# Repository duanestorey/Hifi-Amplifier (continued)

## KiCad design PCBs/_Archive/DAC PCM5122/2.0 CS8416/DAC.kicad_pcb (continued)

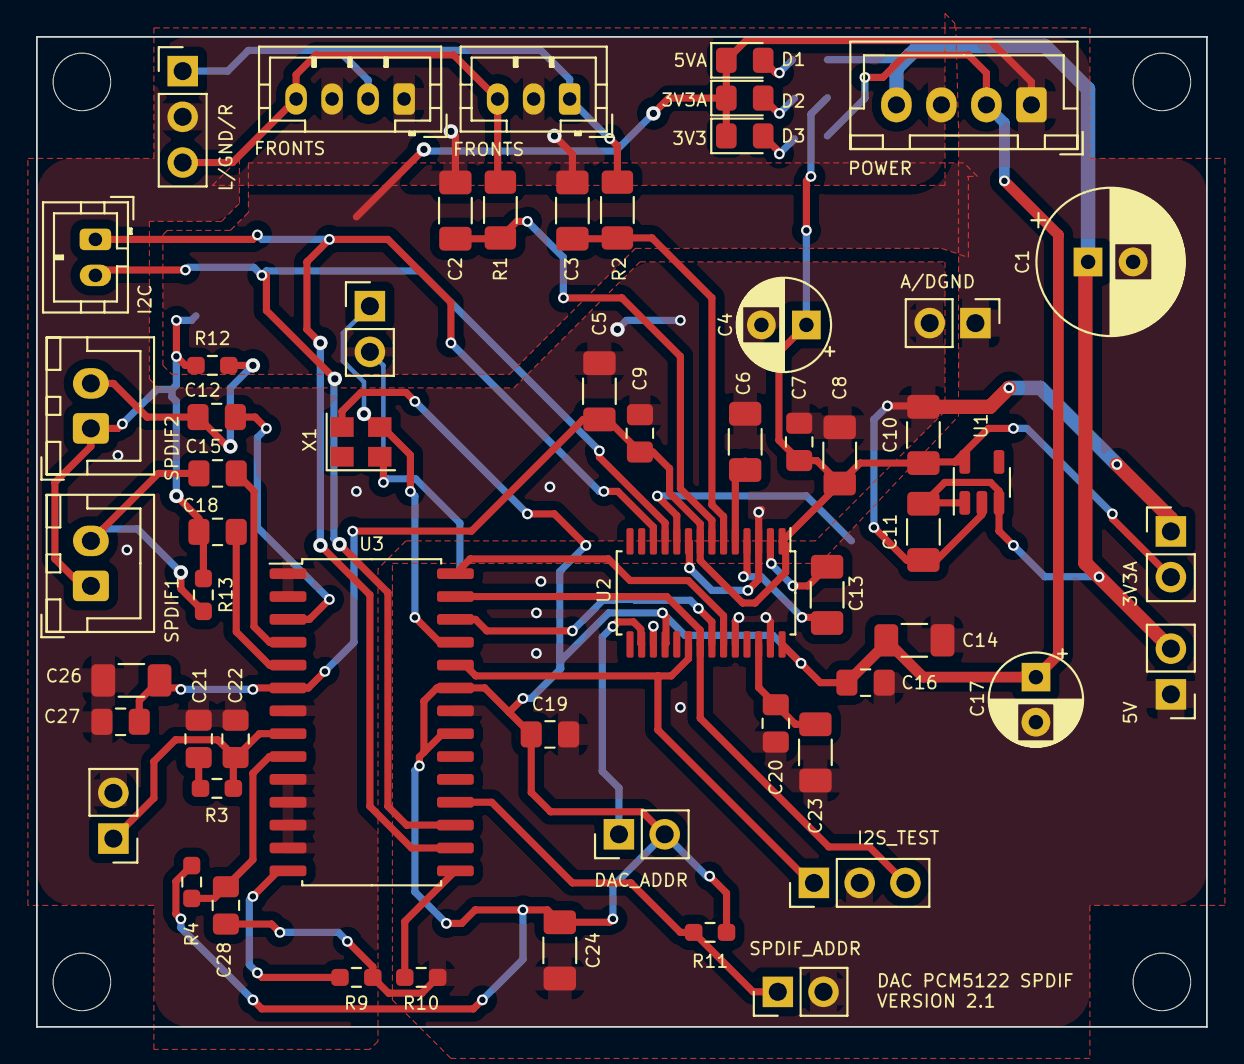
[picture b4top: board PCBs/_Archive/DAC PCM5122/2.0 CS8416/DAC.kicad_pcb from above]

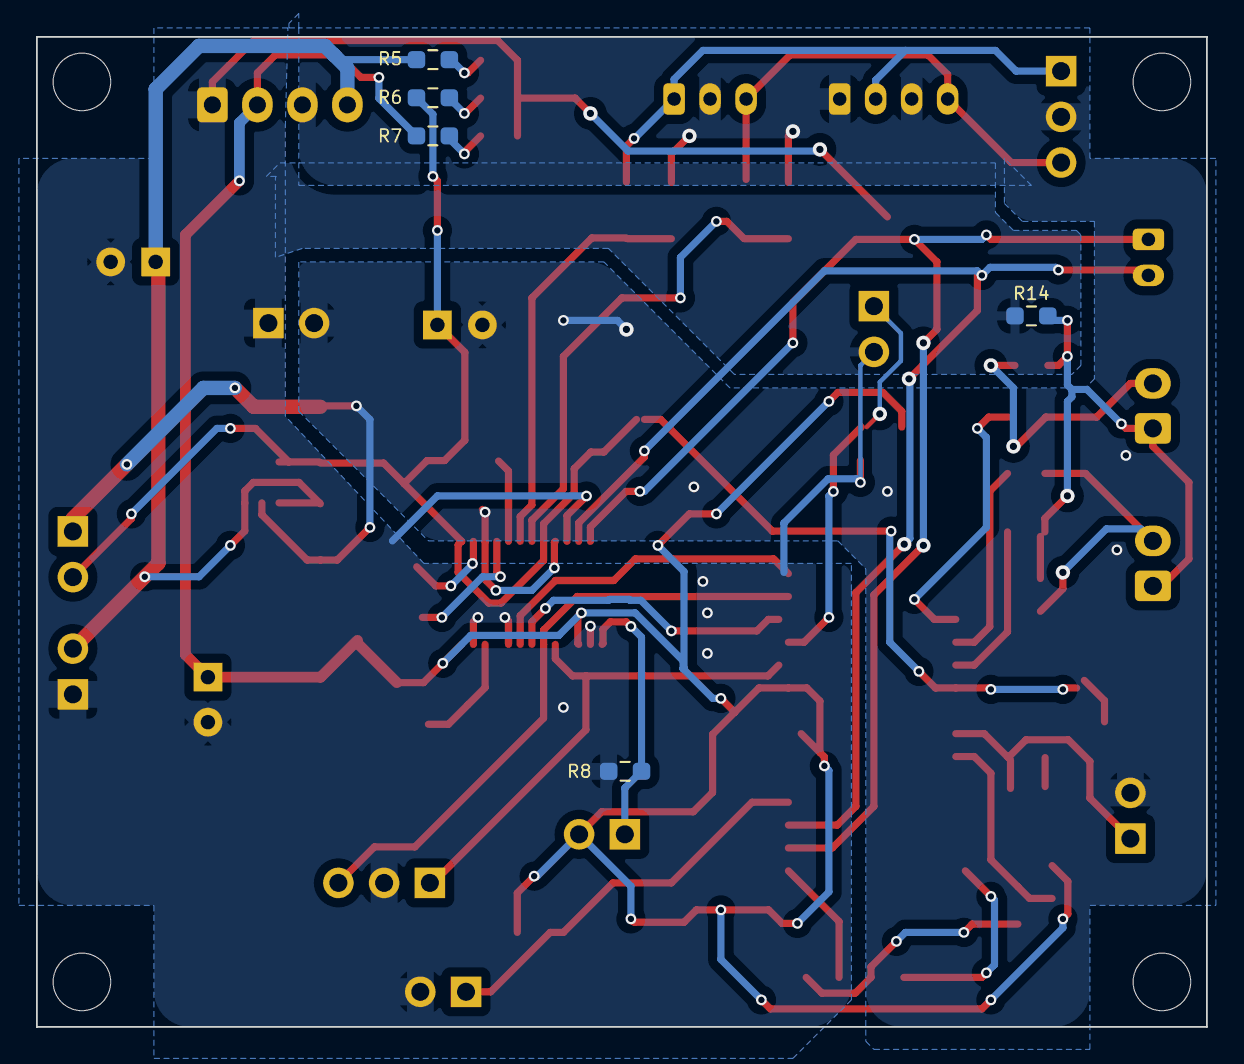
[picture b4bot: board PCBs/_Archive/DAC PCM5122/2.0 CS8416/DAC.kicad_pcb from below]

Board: 2 copper layers, 65.0 x 55.0 mm, 67 parts (5 on the bottom side), 36 nets.

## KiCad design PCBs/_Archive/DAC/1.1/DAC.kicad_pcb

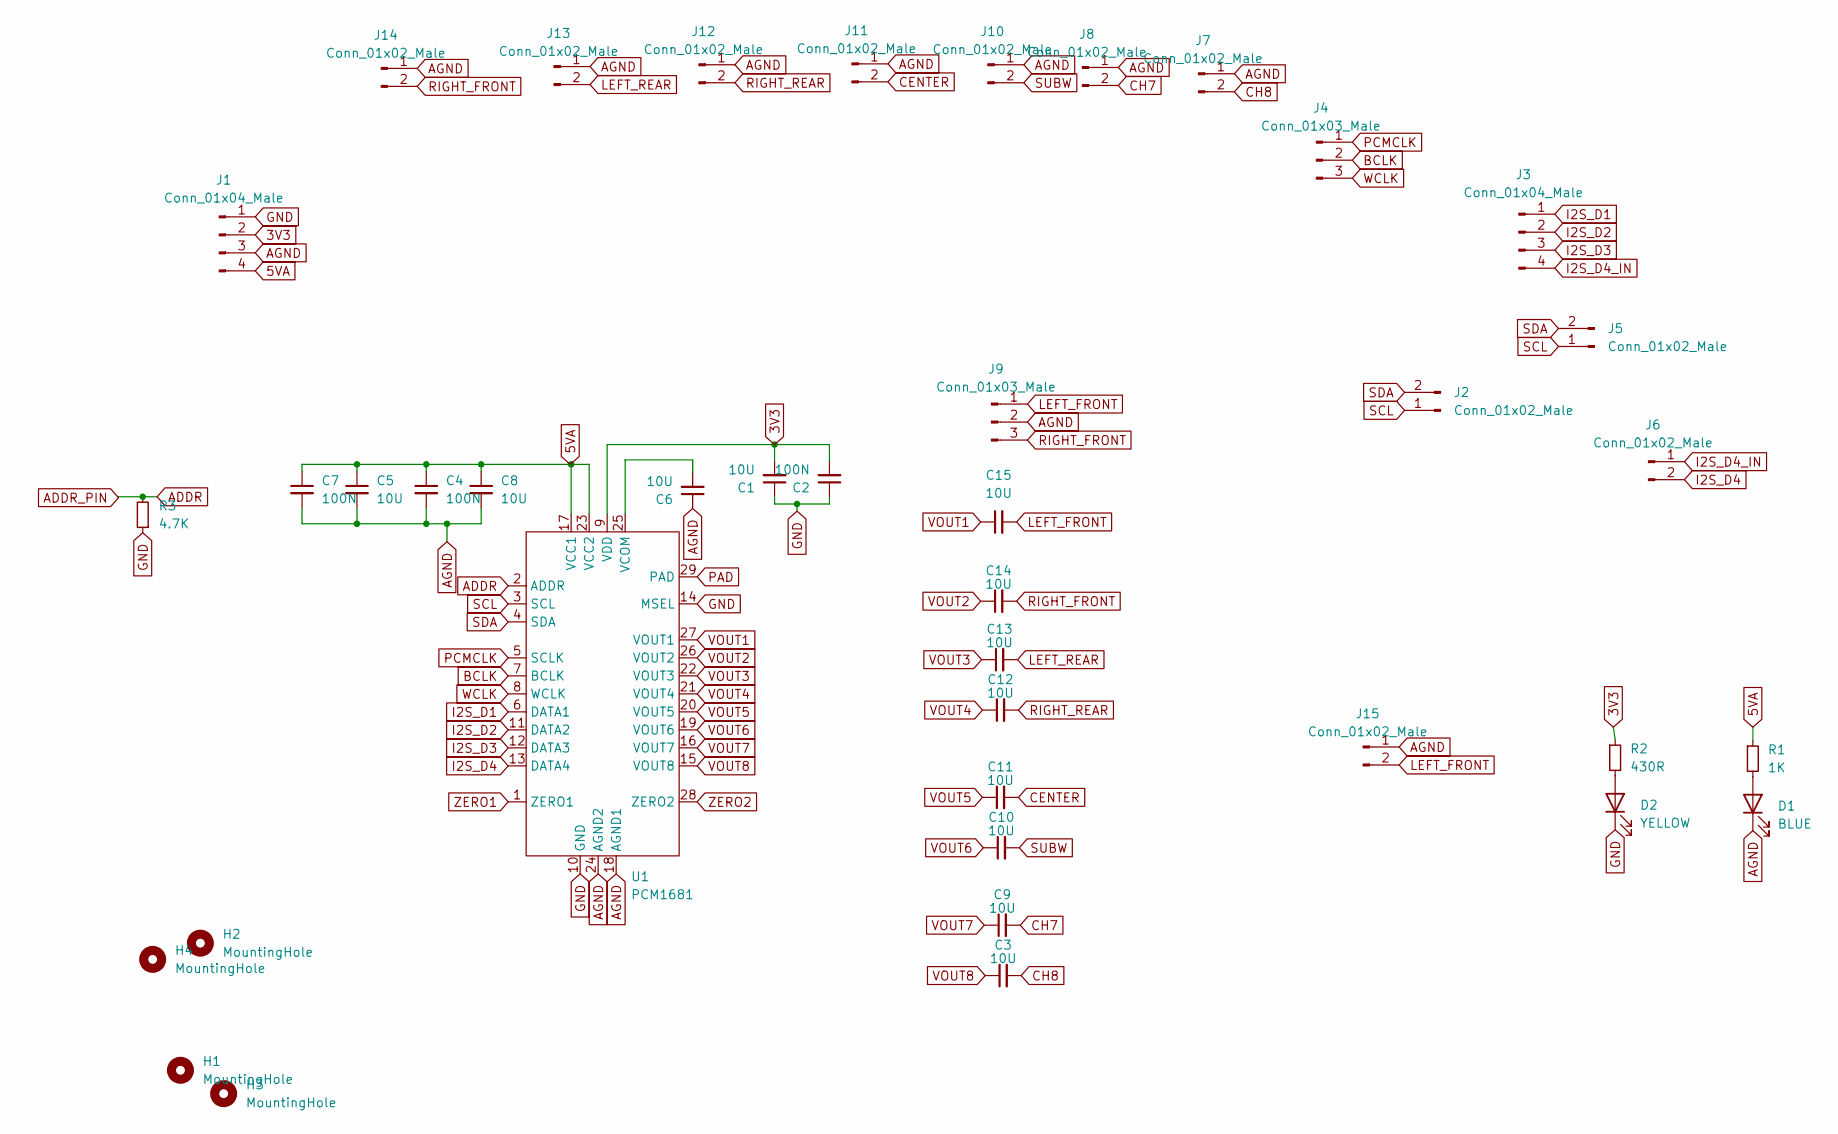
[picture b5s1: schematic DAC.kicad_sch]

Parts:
C1, C5, C6, C8: 10U; C_1206_3216Metric_Pad1.33x1.80mm_HandSolder
C2, C4, C7: 100N; C_0805_2012Metric_Pad1.18x1.45mm_HandSolder
C3, C9, C10, C11, C12, C13, C14, C15: 10U; CP_Radial_D5.0mm_P2.00mm
D1: BLUE; LED_0805_2012Metric_Pad1.15x1.40mm_HandSolder
D2: YELLOW; LED_0805_2012Metric_Pad1.15x1.40mm_HandSolder
H1, H2, H3, H4: MountingHole; MountingHole_3.2mm_M3
J1, J3: Conn_01x04_Male; JST_PH_B4B-PH-K_1x04_P2.00mm_Vertical
J2, J5, J7, J8, J10, J11, J12, J13, J14, J15: Conn_01x02_Male; JST_PH_B2B-PH-K_1x02_P2.00mm_Vertical
J4: Conn_01x03_Male; JST_PH_B3B-PH-K_1x03_P2.00mm_Vertical
J6: Conn_01x02_Male; PinHeader_1x02_P2.54mm_Vertical
J9: Conn_01x03_Male; PinHeader_1x03_P2.54mm_Vertical
R1: 1K; R_0603_1608Metric_Pad0.98x0.95mm_HandSolder
R2: 430R; R_0603_1608Metric_Pad0.98x0.95mm_HandSolder
R3: 4.7K; R_0603_1608Metric_Pad0.98x0.95mm_HandSolder
U1: PCM1681; HTSSOP-28-1EP_4.4x9.7mm_P0.65mm_EP3.4x9.5mm_Mask2.4x6.17mm_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

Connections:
3V3: C1.2, C2.2, J1.2, R2.1, U1.9 (VDD)
5VA: C4.1, C5.1, C7.1, C8.1, J1.4, R1.1, U1.17 (VCC1), U1.23 (VCC2)
ADDR: R3.2, U1.2 (ADDR)
AGND: C4.2, C5.2, C6.1, C7.2, C8.2, D1.1 (K), J1.3, J7.1, J8.1, J9.2, J10.1, J11.1, J12.1, J13.1, J14.1, J15.1, U1.18 (AGND1), U1.24 (AGND2)
BCLK: J4.2, U1.7 (BCLK)
CENTER: C11.2, J11.2
CH7: C9.2, J8.2
CH8: C3.2, J7.2
GND: C1.1, C2.1, D2.1 (K), J1.1, R3.1, U1.10 (GND), U1.14 (MSEL)
I2S_D1: J3.1, U1.6 (DATA1)
I2S_D2: J3.2, U1.11 (DATA2)
I2S_D3: J3.3, U1.12 (DATA3)
I2S_D4: J6.2, U1.13 (DATA4)
I2S_D4_IN: J3.4, J6.1
LEFT_FRONT: C15.2, J9.1, J15.2
LEFT_REAR: C13.2, J13.2
unnamed: D1.2 (A), R1.2
unnamed: D2.2 (A), R2.2
unnamed: C6.2, U1.25 (VCOM)
PAD: U1.29 (PAD)
PCMCLK: J4.1, U1.5 (SCLK)
RIGHT_FRONT: C14.2, J9.3, J14.2
RIGHT_REAR: C12.2, J12.2
SCL: J2.1, J5.1, U1.3 (SCL)
SDA: J2.2, J5.2, U1.4 (SDA)
SUBW: C10.2, J10.2
VOUT1: C15.1, U1.27 (VOUT1)
VOUT2: C14.1, U1.26 (VOUT2)
VOUT3: C13.1, U1.22 (VOUT3)
VOUT4: C12.1, U1.21 (VOUT4)
VOUT5: C11.1, U1.20 (VOUT5)
VOUT6: C10.1, U1.19 (VOUT6)
VOUT7: C9.1, U1.16 (VOUT7)
VOUT8: C3.1, U1.15 (VOUT8)
WCLK: J4.3, U1.8 (WCLK)
ZERO1: U1.1 (ZERO1)
ZERO2: U1.28 (ZERO2)

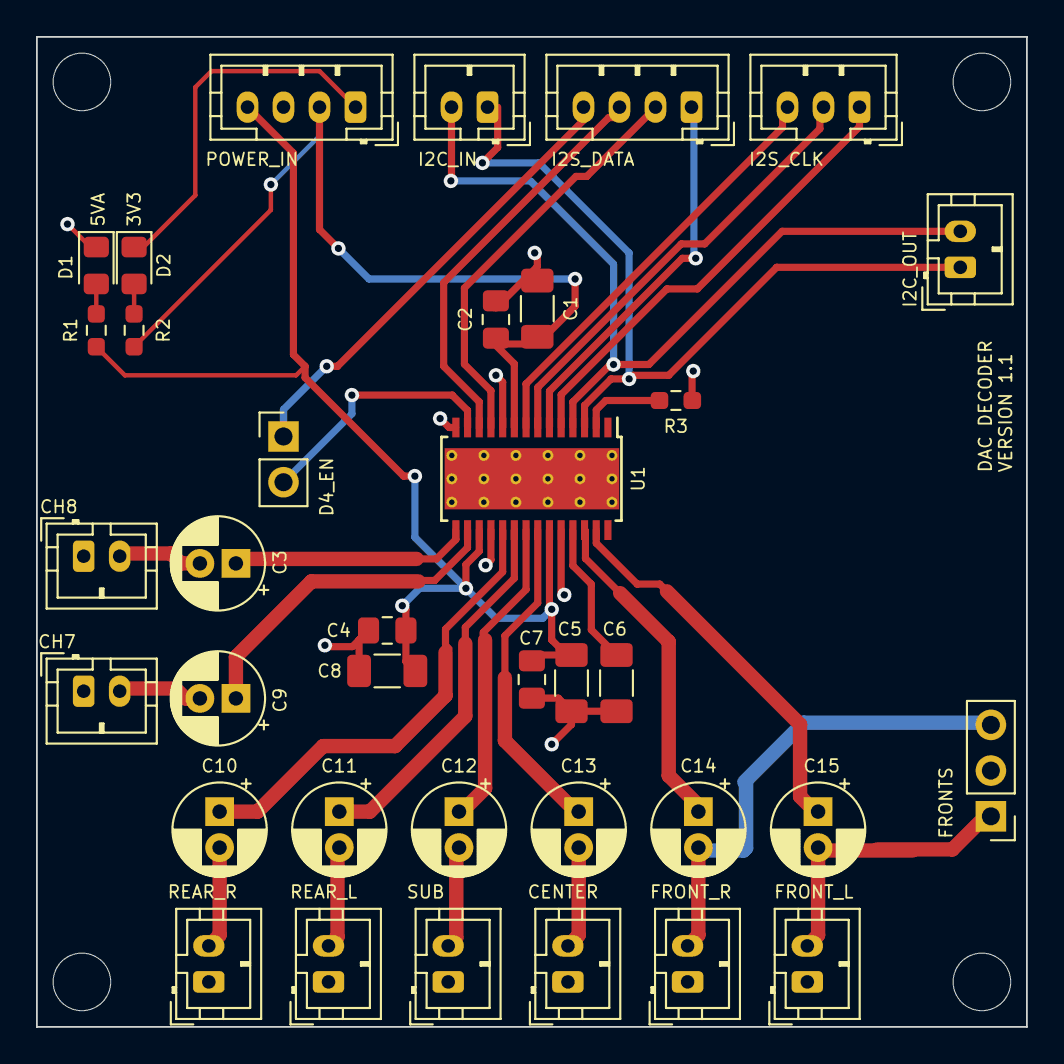
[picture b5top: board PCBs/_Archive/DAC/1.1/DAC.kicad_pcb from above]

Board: 2 copper layers, 55.0 x 55.0 mm, 40 parts (0 on the bottom side), 34 nets.
